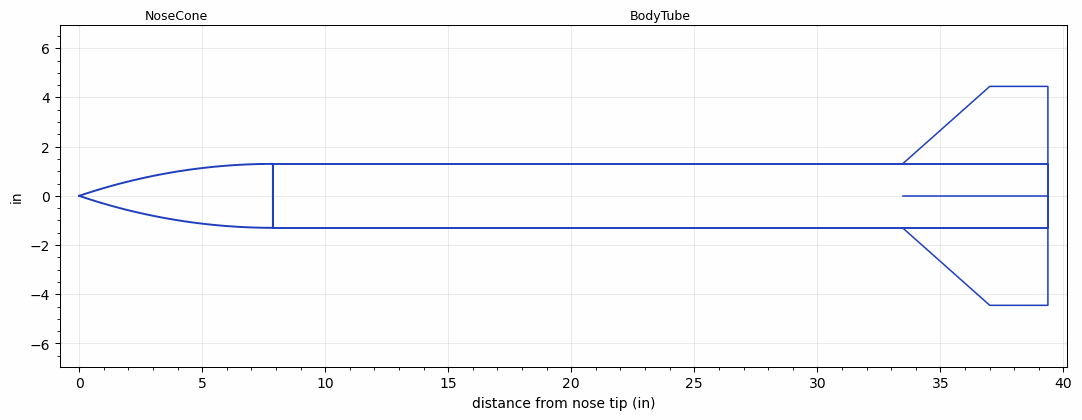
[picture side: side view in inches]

<RASAeroDocument>
 <FileVersion>2</FileVersion>
 <RocketDesign>
  <NoseCone>
   <Length>7.8740157</Length>
   <Diameter>2.5984252</Diameter>
   <Shape>Tangent Ogive</Shape>
   <Location>0</Location>
  </NoseCone>
  <BodyTube>
   <Length>31.496063</Length>
   <Diameter>2.5984252</Diameter>
   <RailGuideDiameter>0.39370079</RailGuideDiameter>
   <RailGuideHeight>0.39370079</RailGuideHeight>
   <Location>7.8740157</Location>
   <Fin>
    <Count>4</Count>
    <Chord>5.9055118</Chord>
    <Span>3.1496063</Span>
    <SweepDistance>3.5433071</SweepDistance>
    <TipChord>2.3622047</TipChord>
    <Thickness>0.15748032</Thickness>
    <Location>5.9055118</Location>
    <AirfoilSection>Square</AirfoilSection>
   </Fin>
  </BodyTube>
  <Surface>Rough Camouflage Paint</Surface>
  <ModifiedBarrowman>False</ModifiedBarrowman>
  <Turbulence>False</Turbulence>
  <UseBooster1>False</UseBooster1>
  <UseBooster2>False</UseBooster2>
  <Comments>Exported by lo-fi-rocket from "r4-scratch-38mm".</Comments>
 </RocketDesign>
 <LaunchSite>
  <Altitude>0</Altitude>
  <Pressure>0</Pressure>
  <RodAngle>0</RodAngle>
  <RodLength>4.9212598</RodLength>
  <Temperature>59</Temperature>
  <WindSpeed>0</WindSpeed>
 </LaunchSite>
 <Recovery>
  <Altitude1>1000</Altitude1>
  <Altitude2>1000</Altitude2>
  <DeviceType1>Parachute</DeviceType1>
  <DeviceType2>None</DeviceType2>
  <Event1>True</Event1>
  <Event2>False</Event2>
  <Size1>35.433071</Size1>
  <Size2>0</Size2>
  <EventType1>Apogee</EventType1>
  <EventType2>None</EventType2>
  <CD1>0.8</CD1>
  <CD2>1.33</CD2>
 </Recovery>
 <SimulationList>
  <Simulation>
   <SustainerEngine>LF-H123W  (LoFi)</SustainerEngine>
   <SustainerLaunchWt>3.0113755</SustainerLaunchWt>
   <SustainerCG>24.607781</SustainerCG>
   <SustainerIgnitionDelay>0</SustainerIgnitionDelay>
   <Booster1SeparationDelay>0</Booster1SeparationDelay>
   <Booster1IgnitionDelay>0</Booster1IgnitionDelay>
   <IncludeBooster1>False</IncludeBooster1>
   <Booster2Delay>0</Booster2Delay>
   <IncludeBooster2>False</IncludeBooster2>
  </Simulation>
 </SimulationList>
</RASAeroDocument>
